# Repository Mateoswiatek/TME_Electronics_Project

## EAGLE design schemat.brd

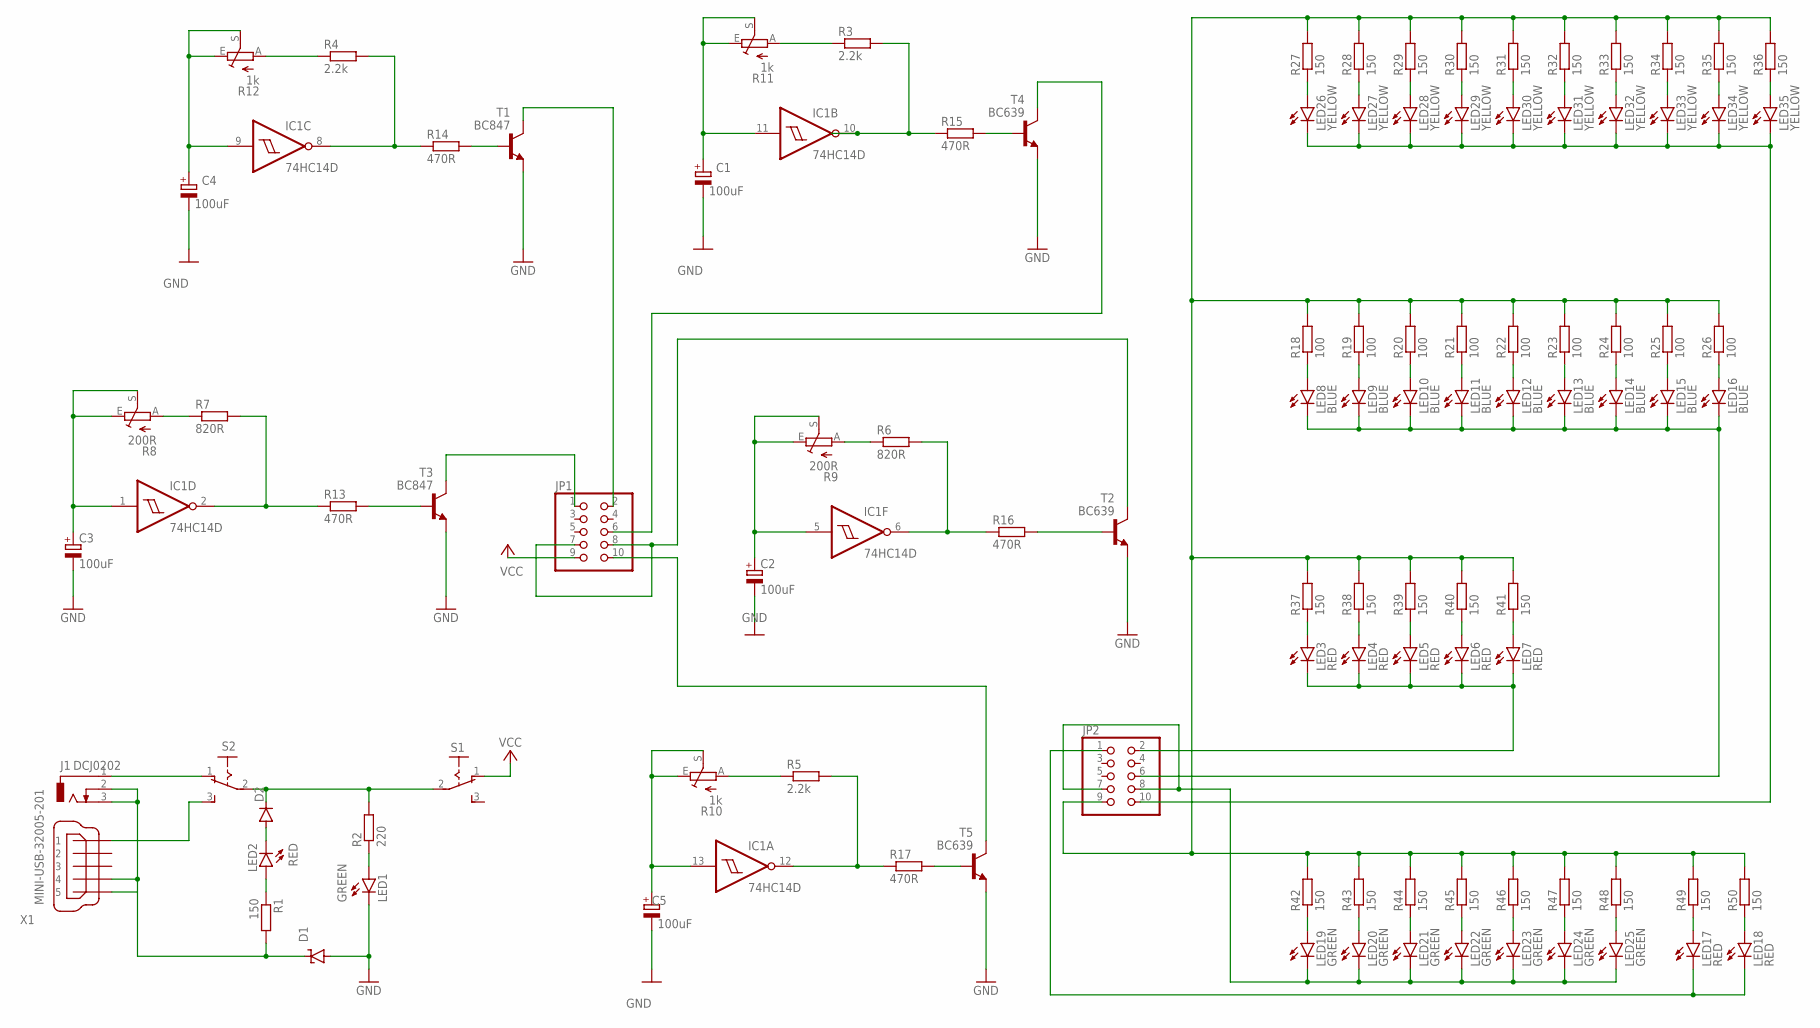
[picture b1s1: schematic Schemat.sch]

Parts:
C1, C2, C3, C4, C5: 100uF; E2,5-6
D1: SUPPRESSOR-SMBJ; SMBJ
D2: DIODE-DO214AC; DO214AC
IC1: 74HC14D; SO14
J1: DCJ0202
JP1: PINHD-2X5; 2X05
JP2: PINHD-2X5/90; 2X05/90
LED1, LED19, LED20, LED21, LED22, LED23, LED24, LED25: GREEN; LED3MM
LED2, LED3, LED4, LED5, LED6, LED7, LED17, LED18: RED; LED5MM
LED8, LED9, LED10, LED11, LED12, LED13, LED14, LED15, LED16: BLUE; LED5MM
LED26, LED27, LED28, LED29, LED30, LED31, LED32, LED33, LED34, LED35: YELLOW; LED5MM
R1, R27, R28, R29, R30, R31, R32, R33, R34, R35, R36, R37, R38, R39, R40, R41, R42, R43, R44, R45, R46, R47, R48, R49, R50: 150; R0805
R2: 220; R0805
R3, R4, R5: 2.2k; R1206
R6, R7: 820R; R1206
R8, R9: 200R; CA6V
R10, R11, R12: 1k; CA6V
R13, R14, R15, R16, R17: 470R; R1206
R18, R19, R20, R21, R22, R23, R24, R25, R26: 100; R0805
S1, S2: M251
T1, T3: BC847; SOT23
T2, T4, T5: BC639; TO92-ECB
X1: MINI-USB-32005-201; 32005-201

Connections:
GND: C1.-, C2.-, C3.-, C4.-, C5.-, D1.A, IC1.7 (GND), LED1.K (C), T1.2 (E), T2.E, T3.2 (E), T4.E, T5.E
unnamed: JP2.2, LED3.K (C), LED4.K (C), LED5.K (C), LED6.K (C), LED7.K (C)
unnamed: JP2.6, LED8.K (C), LED9.K (C), LED10.K (C), LED11.K (C), LED12.K (C), LED13.K (C), LED14.K (C), LED15.K (C), LED16.K (C)
unnamed: D2.A, LED2.K (C)
unnamed: LED2.A, R1.1
unnamed: JP2.9, R18.2, R19.2, R20.2, R21.2, R22.2, R23.2, R24.2, R25.2, R26.2, R27.2, R28.2, R29.2, R30.2, R31.2, R32.2, R33.2, R34.2, R35.2, R36.2, R37.2, R38.2, R39.2, R40.2, R41.2, R42.2, R43.2, R44.2, R45.2, R46.2, R47.2, R48.2, R49.2, R50.2
unnamed: JP2.10, LED26.K (C), LED27.K (C), LED28.K (C), LED29.K (C), LED30.K (C), LED31.K (C), LED32.K (C), LED33.K (C), LED34.K (C), LED35.K (C)
unnamed: JP2.1, LED17.K (C), LED18.K (C)
unnamed: JP2.7, JP2.8, LED19.K (C), LED20.K (C), LED21.K (C), LED22.K (C), LED23.K (C), LED24.K (C), LED25.K (C)
unnamed: LED3.A, R37.1
unnamed: LED21.A, R44.1
unnamed: LED22.A, R45.1
unnamed: LED23.A, R46.1
unnamed: LED24.A, R47.1
unnamed: LED25.A, R48.1
unnamed: LED19.A, R42.1
unnamed: LED20.A, R43.1
unnamed: LED7.A, R41.1
unnamed: LED6.A, R40.1
unnamed: LED5.A, R39.1
unnamed: LED4.A, R38.1
unnamed: D1.C, J1.2, J1.3, R1.2, X1.4, X1.5
unnamed: LED8.A, R18.1
unnamed: LED9.A, R19.1
unnamed: LED10.A, R20.1
unnamed: LED11.A, R21.1
unnamed: LED12.A, R22.1
unnamed: LED13.A, R23.1
unnamed: LED14.A, R24.1
unnamed: LED15.A, R25.1
unnamed: LED16.A, R26.1
unnamed: JP1.2, T1.3 (C)
unnamed: LED18.A, R50.1
unnamed: LED17.A, R49.1
unnamed: D2.C, R2.2, S1.2, S2.2
unnamed: LED27.A, R28.1
unnamed: LED28.A, R29.1
unnamed: LED29.A, R30.1
unnamed: LED30.A, R31.1
unnamed: LED31.A, R32.1
unnamed: LED32.A, R33.1
unnamed: LED33.A, R34.1
unnamed: LED34.A, R35.1
unnamed: LED35.A, R36.1
unnamed: LED26.A, R27.1
unnamed: C1.+, IC1.11 (I), R11.E, R11.S
unnamed: R3.1, R11.A
unnamed: C4.+, IC1.9 (I), R12.E, R12.S
unnamed: R15.2, T4.B
unnamed: IC1.10 (O), R3.2, R15.1
unnamed: R4.1, R12.A
unnamed: R14.2, T1.1 (B)
unnamed: IC1.8 (O), R4.2, R14.1
unnamed: C5.+, IC1.13 (I), R10.E, R10.S
unnamed: R5.1, R10.A
unnamed: R17.2, T5.B
unnamed: IC1.12 (O), R5.2, R17.1
unnamed: R6.1, R9.A
unnamed: R7.1, R8.A
unnamed: IC1.2 (O), R7.2, R13.1
unnamed: R13.2, T3.1 (B)
unnamed: C3.+, IC1.1 (I), R8.E, R8.S
unnamed: IC1.6 (O), R6.2, R16.1
unnamed: R16.2, T2.B
unnamed: C2.+, IC1.5 (I), R9.E, R9.S
unnamed: LED1.A, R2.1
unnamed: JP1.10, T5.C
unnamed: J1.1, S2.1 (O)
unnamed: S2.3 (S), X1.1
unnamed: JP1.6, T4.C
unnamed: JP1.1, T3.3 (C)
unnamed: JP1.7, JP1.8, T2.C
VCC: IC1.14 (VCC), JP1.9, S1.1 (O)

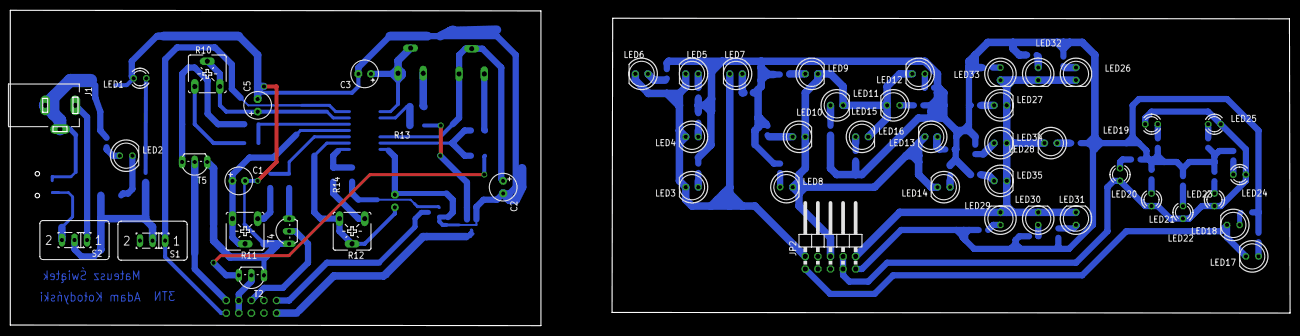
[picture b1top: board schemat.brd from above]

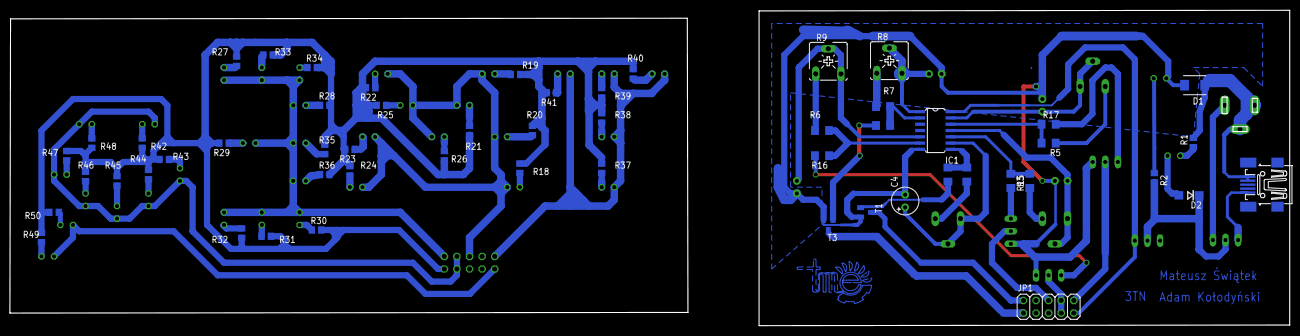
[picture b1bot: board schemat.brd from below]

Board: 2 copper layers, 258.1 x 63.6 mm, 104 parts (55 on the bottom side), 73 nets.
